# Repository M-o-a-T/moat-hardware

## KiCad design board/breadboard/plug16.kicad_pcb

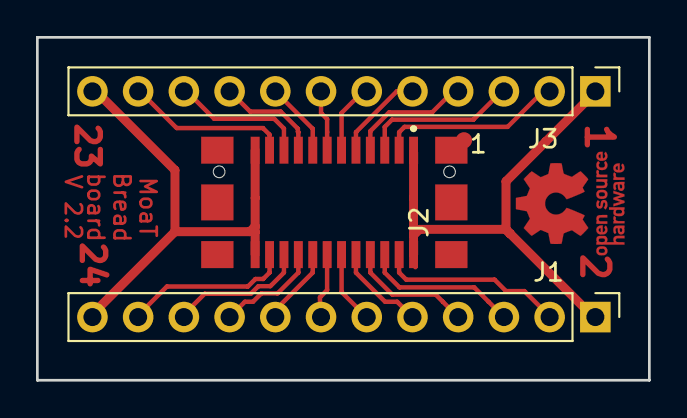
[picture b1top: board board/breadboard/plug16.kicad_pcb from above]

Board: 2 copper layers, 34.0 x 19.1 mm, 3 parts (0 on the bottom side), 22 nets.

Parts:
J1, J3: Conn_01x12; PinHeader_1x12_P2.54mm_Vertical
J2: Moat_Bus_wire; TE_1775014_socket

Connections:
GND: J1.1, J2.1, J2.2, J3.1
GNDPWR: J1.12, J2.23, J2.24, J3.12
unnamed: J1.2, J2.4
unnamed: J1.3, J2.6
unnamed: J1.4, J2.8
unnamed: J1.5, J2.10
unnamed: J1.6, J2.12
unnamed: J1.7, J2.14
unnamed: J1.8, J2.16
unnamed: J1.9, J2.18
unnamed: J1.10, J2.20
unnamed: J1.11, J2.22
unnamed: J2.3, J3.2
unnamed: J2.5, J3.3
unnamed: J2.7, J3.4
unnamed: J2.9, J3.5
unnamed: J2.11, J3.6
unnamed: J2.13, J3.7
unnamed: J2.15, J3.8
unnamed: J2.17, J3.9
unnamed: J2.19, J3.10
unnamed: J2.21, J3.11

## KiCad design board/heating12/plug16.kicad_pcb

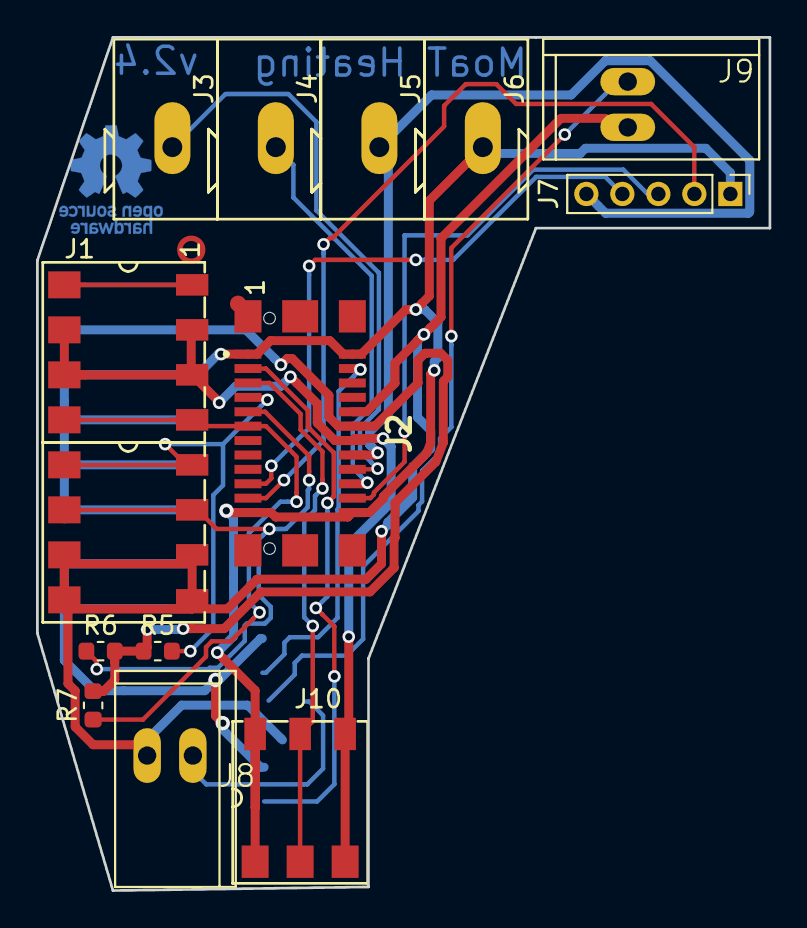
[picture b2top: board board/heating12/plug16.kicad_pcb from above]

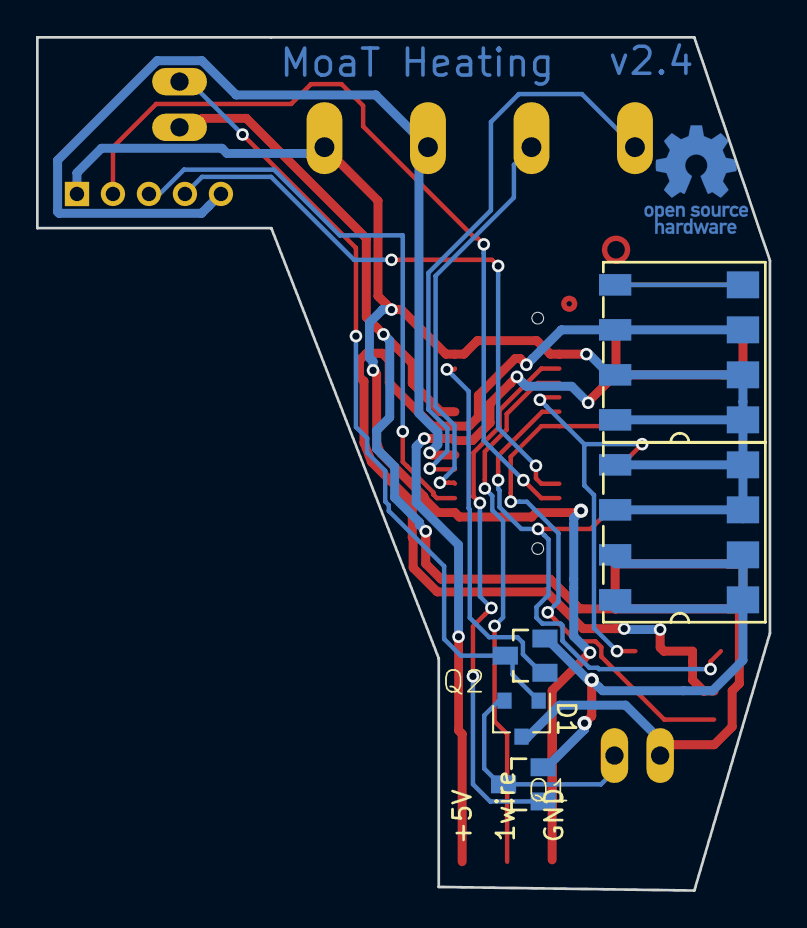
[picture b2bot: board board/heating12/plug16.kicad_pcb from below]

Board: 2 copper layers, 40.7 x 47.4 mm, 16 parts (3 on the bottom side), 19 nets.

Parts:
D1: BAT54C; SOT-23
J1: Moat_Bus_16; Moat_16_2side
J2: Moat_Bus_wire; TE_1775014_socket
J3: SCLK; Wago_Terminal_243
J4: SDA; Wago_Terminal_243
J5: 3V3; Wago_Terminal_243
J6: GND; Wago_Terminal_243
J7: Conn_01x05; PinHeader_1x05_P2.00mm_Vertical
J8: S1; 1X02_GN
J9: S2; 1X02_GN
J10: 1wireConn; AVX_9276_3Pin
Q1, Q2: 2N7002; SOT23
R5, R6, R7: 470; R_0603_1608Metric

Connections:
+5V: J1.3, J1.5, J2.14, J10.3
+12V: J1.4, J2.12, R5.1, R6.2, R7.2
+24V: D1.3, J1.13, J1.15, J2.10, J8.2, J9.2
/S1: J2.3, Q1.1
/S2: J2.4, Q2.1
GND: J1.6, J1.8, J1.10, J1.12, J2.1, J2.2, J2.23, J2.24, J6.1, J7.1, J10.1
GNDPWR: J1.14, J1.16, Q1.2, Q2.2
unnamed: D1.1, J9.1, Q2.3
unnamed: D1.2, J8.1, Q1.3
unnamed: J1.7, J2.11, R7.1
unnamed: J1.9, J2.7, R5.2
unnamed: J1.11, J2.9, R6.1
unnamed: J2.16, J5.1, J7.5
unnamed: J2.18, J3.1
unnamed: J2.19, J7.4
unnamed: J2.20, J4.1
unnamed: J2.21, J7.2
unnamed: J2.22, J7.3
unnamed: J2.5, J10.2

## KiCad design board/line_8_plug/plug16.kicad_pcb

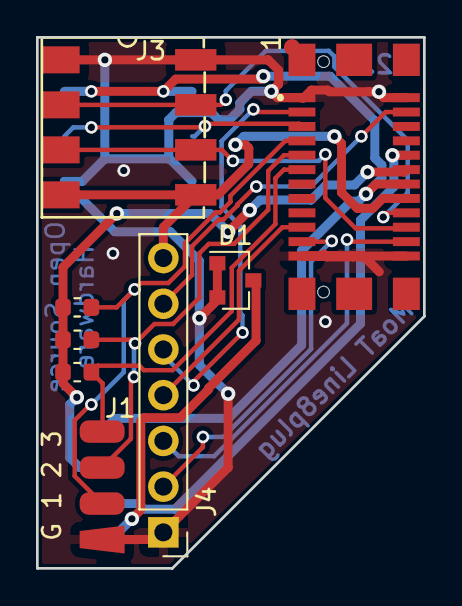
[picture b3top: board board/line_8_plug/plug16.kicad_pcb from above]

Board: 2 copper layers, 21.5 x 29.5 mm, 9 parts (1 on the bottom side), 17 nets.

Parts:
D1: BAT54S; SOT-23
J1: Moat_Bus_8; Moat8-Solder
J2: Moat_Bus_wire; TE_1775014_socket
J3: I2C; AVX_9276_4Pin_HS
J4: Conn_01x07; PinHeader_1x07_P2.54mm_Vertical
J10: 1wireConn; AVX_9276_3Pin
R5, R6, R7: 470; R_0603_1608Metric

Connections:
+3V3: J2.16, J3.4, J4.7
+5V: J1.5, J2.14, J10.3
+12V: J1.6, J2.12, R5.2, R6.2, R7.2
+24V: J1.7, J2.10
GND: D1.1, D1.2, J1.1, J2.1, J2.2, J2.23, J2.24, J3.1, J4.1, J10.1
GNDPWR: D1.3, J1.8
unnamed: J1.2, J2.7, R7.1
unnamed: J1.3, J2.9, R5.1
unnamed: J1.4, J2.11, R6.1
unnamed: J2.3, J4.5
unnamed: J2.4, J4.6
unnamed: J2.18, J3.2
unnamed: J2.19, J4.4
unnamed: J2.20, J3.3
unnamed: J2.21, J4.2
unnamed: J2.22, J4.3
unnamed: J2.5, J10.2

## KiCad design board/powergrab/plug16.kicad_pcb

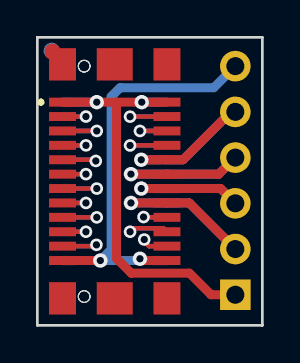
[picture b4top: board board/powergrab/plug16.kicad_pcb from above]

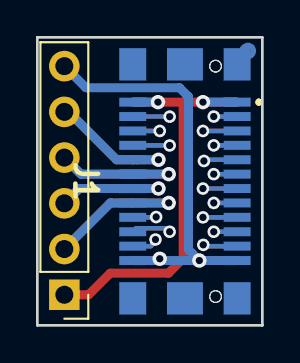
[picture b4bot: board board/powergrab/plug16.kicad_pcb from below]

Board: 2 copper layers, 12.5 x 16.0 mm, 3 parts (2 on the bottom side), 22 nets.

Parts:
J1: Moat_Bus_device; TE_1775013_plug
J2: Moat_Bus_wire; TE_1775014_socket
J3: Conn_01x06; PinHeader_1x06_P2.54mm_Vertical

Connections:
+3V3: J1.16, J2.16, J3.2
+5V: J1.14, J2.14, J3.3
+12V: J1.12, J2.12, J3.4
+24V: J1.10, J2.10, J3.5
GND: J1.1, J1.2, J2.1, J2.2, J3.1
GNDPWR: J1.23, J1.24, J2.23, J2.24, J3.6
unnamed: J1.3, J2.3
unnamed: J1.4, J2.4
unnamed: J1.5, J2.5
unnamed: J1.6, J2.6
unnamed: J1.7, J2.7
unnamed: J1.8, J2.8
unnamed: J1.9, J2.9
unnamed: J1.11, J2.11
unnamed: J1.13, J2.13
unnamed: J1.15, J2.15
unnamed: J1.17, J2.17
unnamed: J1.18, J2.18
unnamed: J1.19, J2.19
unnamed: J1.20, J2.20
unnamed: J1.21, J2.21
unnamed: J1.22, J2.22

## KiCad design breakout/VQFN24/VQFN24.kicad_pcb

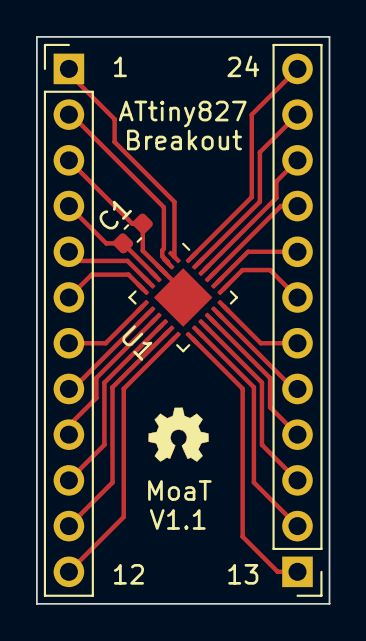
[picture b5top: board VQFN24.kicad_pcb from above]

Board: 2 copper layers, 16.3 x 31.5 mm, 4 parts (0 on the bottom side), 24 nets.

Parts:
C1: CP_1µ_10V_0603; C_0603_1608Metric
J1a1, J1b1: Conn_01x12_Male; PinHeader_1x12_P2.54mm_Vertical
U1: ATtiny827-M; QFN-24-1EP_4x4mm_P0.5mm_EP2.6x2.6mm

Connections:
unnamed: J1a1.6, U1.6 (PA5)
unnamed: J1a1.7, U1.7 (PA6)
unnamed: J1a1.8, U1.8 (PA7)
unnamed: J1a1.9, U1.9 (PB7)
unnamed: J1a1.10, U1.10 (PB6)
unnamed: J1a1.11, U1.11 (PB5)
unnamed: J1a1.12, U1.12 (PB4)
unnamed: J1b1.2, U1.14 (PB2)
unnamed: J1b1.3, U1.15 (PB1)
unnamed: J1b1.4, U1.16 (PB0)
unnamed: J1b1.11, U1.23 (~RESET/PA0)
unnamed: C1.2, J1a1.3, U1.3 (GND), U1.25 (GND)
unnamed: J1b1.12, U1.24 (PA1)
unnamed: J1a1.1, U1.1 (PA2)
unnamed: J1a1.2, U1.2 (PA3)
unnamed: J1a1.5, U1.5 (PA4)
unnamed: J1b1.1, U1.13 (PB3)
unnamed: J1b1.5, U1.17 (PC0)
unnamed: J1b1.6, U1.18 (PC1)
unnamed: J1b1.7, U1.19 (PC2)
unnamed: J1b1.8, U1.20 (PC3)
unnamed: J1b1.9, U1.21 (PC4)
unnamed: J1b1.10, U1.22 (PC5)
unnamed: C1.1, J1a1.4, U1.4 (VCC)
